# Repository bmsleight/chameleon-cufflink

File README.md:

# chameleon-cufflink
Cufflinks that can change colour

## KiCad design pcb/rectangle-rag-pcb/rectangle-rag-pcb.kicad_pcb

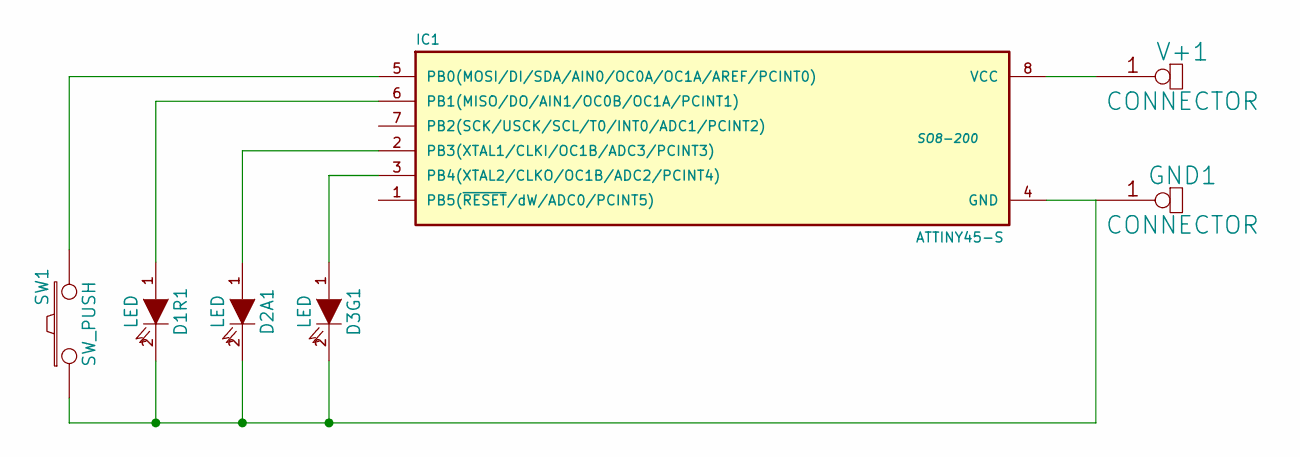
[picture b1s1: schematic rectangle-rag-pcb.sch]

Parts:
D1R1, D2A1, D3G1: LED
GND1: CONNECTOR
IC1: ATTINY45-S; SO8-200
SW1: SW_PUSH
V+1: CONNECTOR

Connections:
unnamed: D1R1.2 (K), D2A1.2 (K), D3G1.2 (K), GND1.1, IC1.4 (GND), SW1.1
unnamed: IC1.8 (VCC), V+1.1
unnamed: D1R1.1 (A), IC1.6 (PB1(MISO/DO/AIN1/OC0B/OC1A/PCINT1))
unnamed: IC1.5 (PB0(MOSI/DI/SDA/AIN0/OC0A/OC1A/AREF/PCI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), SW1.2
unnamed: D2A1.1 (A), IC1.2 (PB3(XTAL1/CLKI/OC1B/ADC3/PCINT3))
unnamed: D3G1.1 (A), IC1.3 (PB4(XTAL2/CLKO/OC1B/ADC2/PCINT4))

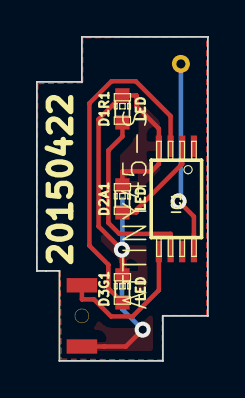
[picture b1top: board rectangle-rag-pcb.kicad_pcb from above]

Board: 2 copper layers, 9.5 x 18.0 mm, 7 parts (1 on the bottom side), 6 nets.

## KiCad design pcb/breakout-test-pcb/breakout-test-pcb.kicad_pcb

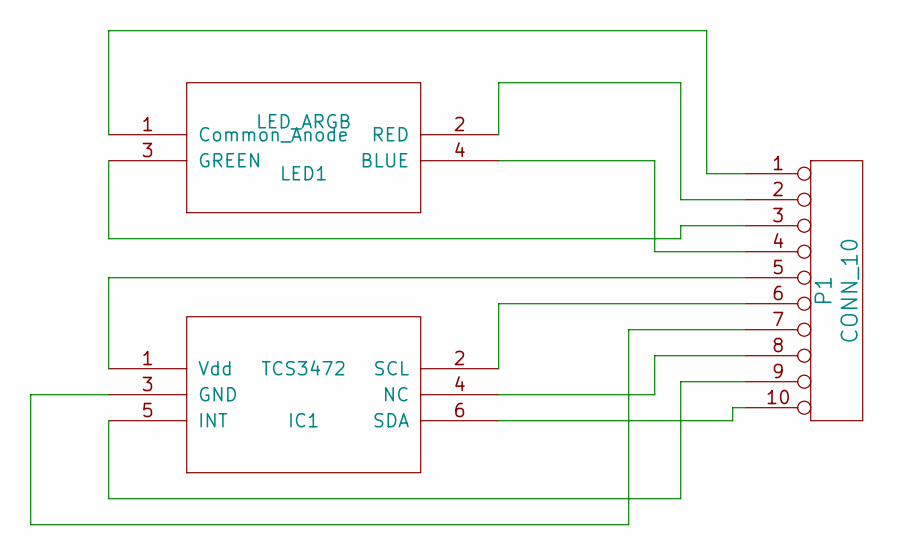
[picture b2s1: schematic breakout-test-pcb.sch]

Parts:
IC1: TCS3472; MODULE
LED1: LED_ARGB; MODULE
P1: CONN_10

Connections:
unnamed: LED1.3 (GREEN), P1.3
unnamed: LED1.4 (BLUE), P1.4
unnamed: IC1.1 (Vdd), P1.5
unnamed: IC1.2 (SCL), P1.6
unnamed: IC1.3 (GND), P1.7
unnamed: IC1.4 (NC), P1.8
unnamed: IC1.5 (INT), P1.9
unnamed: IC1.6 (SDA), P1.10
unnamed: LED1.2 (RED), P1.2
unnamed: LED1.1 (Common_Anode), P1.1

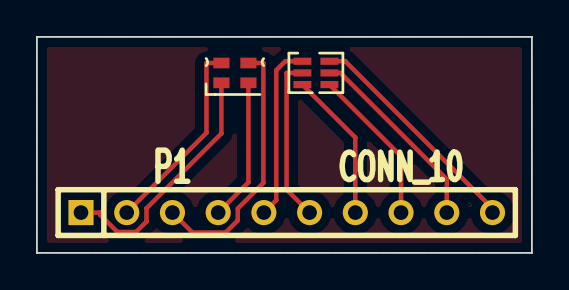
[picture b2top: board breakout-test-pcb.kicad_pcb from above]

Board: 2 copper layers, 27.5 x 12.0 mm, 3 parts (0 on the bottom side), 10 nets.

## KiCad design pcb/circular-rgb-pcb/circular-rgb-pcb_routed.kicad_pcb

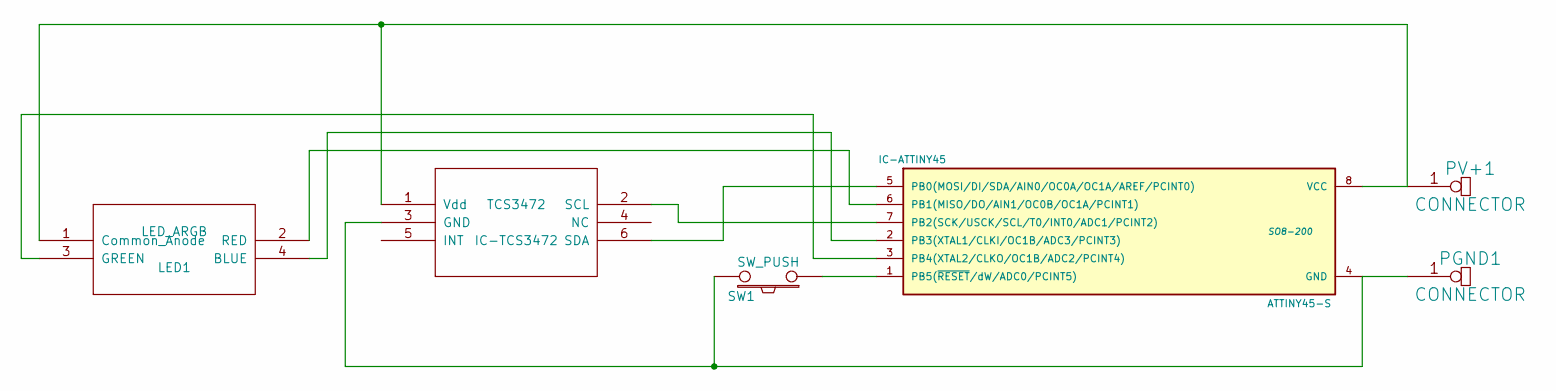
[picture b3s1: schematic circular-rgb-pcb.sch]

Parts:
IC-ATTINY45: ATTINY45-S; SO8-200
IC-TCS3472: TCS3472; MODULE
LED1: LED_ARGB; MODULE
PGND1: CONNECTOR
PV+1: CONNECTOR
SW1: SW_PUSH

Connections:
unnamed: IC-ATTINY45.6 (PB1(MISO/DO/AIN1/OC0B/OC1A/PCINT1)), LED1.2 (RED)
unnamed: IC-ATTINY45.5 (PB0(MOSI/DI/SDA/AIN0/OC0A/OC1A/AREF/PCI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), IC-TCS3472.6 (SDA)
unnamed: IC-ATTINY45.7 (PB2(SCK/USCK/SCL/T0/INT0/ADC1/PCINT2)), IC-TCS3472.2 (SCL)
unnamed: IC-ATTINY45.2 (PB3(XTAL1/CLKI/OC1B/ADC3/PCINT3)), LED1.4 (BLUE)
unnamed: IC-ATTINY45.3 (PB4(XTAL2/CLKO/OC1B/ADC2/PCINT4)), LED1.3 (GREEN)
unnamed: IC-ATTINY45.8 (VCC), IC-TCS3472.1 (Vdd), LED1.1 (Common_Anode), PV+1.1
unnamed: IC-ATTINY45.1 (PB5(~RESET~/dW/ADC0/PCINT5)), SW1.1
unnamed: IC-ATTINY45.4 (GND), IC-TCS3472.3 (GND), PGND1.1, SW1.2

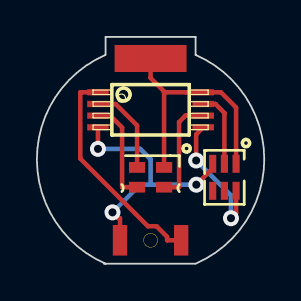
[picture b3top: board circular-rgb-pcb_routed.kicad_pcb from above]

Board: 2 copper layers, 12.6 x 12.6 mm, 6 parts (1 on the bottom side), 8 nets.

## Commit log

2015-03-22 Initial PCB files
2015-03-22 Breakout board added
2015-04-05 Adding first sketch
2015-04-06 Still playign wiht PWM
2015-04-06 Still playing wiht PWM
2015-04-12 Addign Laser outline
2015-04-12 Adding Laser outline
2015-04-12 Updating Laser outline
2015-04-15 Updating case
2015-04-16 Adding serial numbers
2015-04-19 Adding simple-random-colours
2015-04-22 Adding rectangle-rag-pcb v20150422
2015-04-23 Adding 1st draft of circular-rgb-pcb
2015-04-25 Adding laser_RAG.py
2015-04-25 Updating laser_RAG.py
2015-04-26 Updateing circular PCB, includign gerber-set
2015-04-26 Updating Laser clear
2015-04-26 Updating Laser RGB
2015-05-04 Adding breakout-test-pcb-LTC3212
2015-05-05 Adding first rectangle_rag sketch
2015-05-05 Updating rectangle to use PROGMEM and lookup table
2015-05-06 Stop that Flash Jitter
2015-05-06 Flashes
2015-05-06 Adding button pushes
2015-05-07 Updating how button works.
2015-05-16 Adding sleep functions
